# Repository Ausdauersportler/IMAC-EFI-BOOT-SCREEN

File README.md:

# IMAC-EFI-BOOT-SCREEN

How to create an EFI boot screen vBIOS for Apple 2009 to Mid 2011 iMac systems using AMD MXM3 graphics cards

My goal is to provide a comprehensive guide how to construct EFI BIOS versions for some AMD MXM cards. As described in detail in this [thread](https://forums.macrumors.com/threads/2011-imac-graphics-card-upgrade.1596614/post-17425857) owners of modular Apple iMac models built in 2009-2011 with MXM slot graphcs card can replace the original ATI card either with an Nvidia Kepler or an AMD GCN 1.0 to 4.0 card. While there has been a lot of success offering an EFI boot screen with NVIDIA cards development stuck with the AMD cards at some point where an iMac firmware modification has been proposed. Although the firmware modification is quite simple the adoption rate is frankly speaking zero. IMHO this is still the best way to go. Nevertheless even this method will need a BIOS constructed in the same way as described here within the wiki. 

Just to complete this introduction: 
Lately [improvements](https://forums.macrumors.com/threads/imac-2011-maxwell-and-pascal-gpu-upgrade.2300989/post-30017630) have been made to add a NVIDIA Maxwell and Pascal card, but please note there are no macOS drivers available within any macOS versions starting with Mojave, and there is limited EFI boot screen support.

The [wiki](https://github.com/Ausdauersportler/IMAC-EFI-BOOT-SCREEN/wiki) decribes tools, sources, methods, orignal limitations, solutions and state of the current development.  

## iMac models supported

This repository is limited to these eight iMac models published from 2009 to 2011:

- iMac9,1 Early 2009 A1225 24 inch (LVDS) (using a modified EnableGop9,1 driver, see note 1)
- iMac10,1 Late 2009 A1311 21.5 inch (LVDS) (see note 2)

- iMac10,1 Late 2009 A1312 27 inch (eDP, see note 3 about EG2)

- iMac11,1 Late 2009 A1312 27 inch (eDP)
- iMac11,2 Mid 2010 A1311 21.5 inch (eDP)
- iMac11,3 Mid 2010 A1312 27 inch (eDP)

- iMac12,1 Mid 2011 A1311 21.5 inch (eDP)
- iMac12,2 Mid 2011 A1312 27 inch (eDP)

Notes: 

1. Finally it was possible to include the iMac9,1 Mid 2009 A1225 24 inch to this list. The [2.93 GHz](https://everymac.com/systems/apple/imac/specs/imac-core-2-duo-3.06-24-inch-aluminum-early-2009-specs.html) and [3.06 GHz](https://everymac.com/systems/apple/imac/specs/imac-core-2-duo-2.93-24-inch-aluminum-early-2009-specs.html) versions were equipped with MXM3 slots and non metal graphics cards (GT120, GT130, AMD 4850). Best cards to use are the AMD FirePro M4000, M5100, W5170M, and M6000. The power hungry Saturn cards M6100 and W6170M/W6150M will over heat the system under load rapidly. This system needs a special EnableGop91 driver. All vBIOS files are marked aka named like this and include the LVDS string, too. Some more recent NVIDIA MXM3 cards may still have LVDS signaling support and therfore may work with these iMac9,1 system, too (never tested).

2. vBIOS file names contain the string LVDS, but not show the EnableGop91 string (see note 1). Unfortunately all more recent AMD GPUS starting the the Polaris/GCN4 architecture lack LVDS signaling hardware support. Therefore you cannot get those cards to display the boot screen unless you connect the internal display using a third party display driver board the external DP port - making it an externally connected display.

3. EG2 versions of vBIOS do not run on iMac10,1 A1312 systems, you get only a white screen in power on/boot. EG versions support all types of Macs listed.

4. Althout one cannot modify the legacy part of the vBIOS it is possible to inject a modified legacy vBIOS (the first 64K of it) using an SSDT or OpenCore DeviceProperties (ATY,bin_image) to enable the backlight control on Big Sur and Monterey. This mod does not apply or work with any Windows installation. Adding the EnableGop driver brought back EFI boot screen support. First and only replacement card which enables both external display connectors on iMac12,2.

5. Same method as described above enables virtual brightness control on RX6600M. Although values in ioreg and NVRAM are changed the brightness of the display itself does not change, probably because MXM PINS 23,25,27 are not connected as described in this [video](https://www.bilibili.com/video/BV1Ec411d7z6). Additionally the GOP driver has to be patched with the [Syncretic tool](https://forums.macrumors.com/threads/amd-radeon-rx-6800-xt-6900-xt-for-macos.2262295/page-36?post=31039294#post-31039294). Unfortunately neither EnableGop not OpenCore are able to switch on the internal backlight, so the display comes to life late at the login screen. 

## AMD graphcis cards supported

Currently we have tested these cards and can confirm the method works with:

- AMD FirePro M4000
- AMD FirePro M5100
- AMD FirePro M6000
- AMD FirePro W5170M

- AMD FirePro M6100
- AMD FirePro W6150M
- AMD FirePro W6170M

- AMD FirePro W7170M 
- AMD FirePro S7100X

- AMD Radeon Pro WX4130 mobile
- AMD Radeon Pro WX4150 mobile
- AMD Radeon Pro WX4170 mobile

- AMD Radeon Pro WX3200 mobile

- AMD Radeon Pro RX470 mobile
- AMD Radeon Pro RX480 mobile
- AMD Radeon Pro WX7100 mobile

- AMD Radeon Pro RX5500XT mobile (see note 4 above)
- AMD Radeon Pro RX6600M mobile (see note 5 above)

## Hardware upgrade (wiki)

You will find an [overwiew](https://github.com/Ausdauersportler/IMAC-EFI-BOOT-SCREEN/wiki/WWWW) which card works in which iMac and how to start the upgrade project and some more hardware related information about minor soldering tasks needed for a few cards to make them fully compatible in a newly added hardware section.

## Credits

Most knowledge has been gathered by me from contributions made by [Nick [D]vB](https://github.com/iMacGFX), [nikey22](https://github.com/nikey22), and [internetzel](https://github.com/internetzel) who spent some nights to explain everything in detail to me and who has much more patience to dive deeply into this matter than I do. Hope he will join me to fill this repository with contents. Last but not least thanks to [dfranetic](https://github.com/franetic), he finished what I could not have done. Great team!

Thanks to [rthpjm](https://forums.macrumors.com/members/rthpjm.535915/) for finding a W6150M and the necessary legacy vBIOS in some HP firmware update. Special thanks to [edwardgeo](https://forums.macrumors.com/members/edwardgeo.1274066/) for countless ideas and incredible knowledge about indepth AMD vBIOS modifications. All the best if these dark times!

[m0bil](https://github.com/m0bil) has become the expert for all NVIDIA modifications and probably he should start a similar repository about it and more importantly to this project he is the undisputed master of all iMac firmware modifications.

Finally many thanks to [Mike Beaton](https://github.com/mikebeaton) who developed an EFI driver named [EnableGop](https://github.com/mikebeaton/OpenCorePkg/tree/master/Staging/EnableGop) usable for both MacPro5,1 and modular iMacs as listed above using either Nvidia or AMD graphics cards to enable the EFI boot picker. I had to modify this driver a little bit to make it work on the older (LVDS) iMac9,1 model. This change has not been included into the EnableGop source tree and you need to get the driver named EnableGop91 compiled from this page. It works as desigend, with AMD and likely with NVIDIA cards as well.

## Support

If you want to support the AMD (i)Mac vBIOS development or just buy me a coffee [donations](https://www.paypal.com/paypalme/Ausdauersportler) are greatly appreciated.

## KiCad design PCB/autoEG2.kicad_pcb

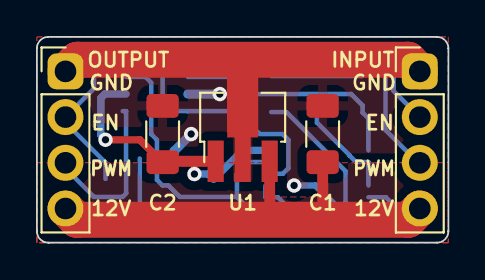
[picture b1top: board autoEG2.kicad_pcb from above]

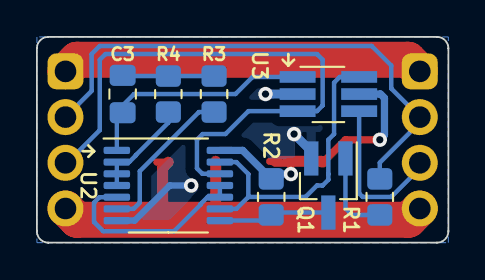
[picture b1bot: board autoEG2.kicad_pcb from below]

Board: 2 copper layers, 22.9 x 11.4 mm, 13 parts (8 on the bottom side), 14 nets.

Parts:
C1, C2: 1u; C_1206_3216Metric_Pad1.33x1.80mm_HandSolder
C3: 1nF; C_0805_2012Metric_Pad1.18x1.45mm_HandSolder
INPUT: Conn_01x04_Male; PinHeader_1x04_P2.54mm_Vertical
OUTPUT: Conn_01x04_Male; PinHeader_1x04_P2.54mm_Vertical
Q1: MMBT3904; SOT-23_Handsoldering
R1: 47k; R_0805_2012Metric_Pad1.20x1.40mm_HandSolder
R2: 22k; R_0805_2012Metric_Pad1.20x1.40mm_HandSolder
R3: 330k; R_0805_2012Metric_Pad1.20x1.40mm_HandSolder
R4: 33k; R_0805_2012Metric_Pad1.20x1.40mm_HandSolder
U1: L78L33; SOT-89-3_Handsoldering
U2: 74HC02; TSSOP-14_4.4x5mm_P0.65mm
U3: 74LVC1G157; TSOT-23-6_HandSoldering

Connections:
+12V: C1.1, INPUT.4, OUTPUT.4, U1.3 (IN)
/Q: U2.5, U2.10, U2.11
/R: Q1.3 (C), R2.2, U2.8
/S: INPUT.3, U2.12, U3.3 (I0)
/~Q: U2.9, U2.13, U3.6 (S)
GND: C1.2, C2.2, INPUT.1, OUTPUT.1, Q1.2 (E), U1.2 (GND), U2.7 (GND), U3.2 (GND)
unnamed: C3.1, U2.1, U3.1 (I1)
unnamed: C3.2, R3.2, R4.2
unnamed: Q1.1 (B), R1.2
unnamed: INPUT.2, OUTPUT.2, R1.1
unnamed: R3.1, U2.6
unnamed: R4.1, U2.2, U2.3, U2.4
unnamed: OUTPUT.3, U3.4 (Y)
VCC: C2.1, R2.1, U1.1 (OUT), U2.14 (VCC), U3.5 (VCC)

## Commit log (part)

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2022-04-12 Update README.md
    Added W7170M/S7100X and applied some minor corrections.
2022-04-12 Create empty
2022-04-12 Add files via upload
    wiki documentation image
2022-04-12 Hex Fiend
    Searching the frame buffer name and supported device-id
2022-04-13 Add files via upload
    unmodified EFI module extracted from MacBookPro 15" 2015 firmware
2022-04-13 Add files via upload
    Modified version of the VenusEG2.efi as described in the documentation ready to use within the EFI BIOS.
2022-04-13 Add files via upload
    EFirom compressed version of M370.efi with device-id 0x6820.
2022-04-13 Add files via upload
    EFIrom macOS executable (terminal, in case you cannot start it adjust permissions using chmod)
2022-04-13 Add files via upload
    modules ready to inject into iMac firmware
2022-04-13 Add files via upload
    CoreEG2 and EDIDParser modules in EFI format (just a different header compared to the similar ffs modules uploaded). These files can be used with OpenCore.
2022-04-13 Add files via upload
    W5170M iMac compatible GOP BIOS ((c) Ausdauersportler 2021)
2022-04-13 Add files via upload
    iMac compatible EG2 BIOS ((c) Ausdauersportler 2021)
2022-04-13 Add files via upload
    Replace the GOP with the Apple EG2 BIOS
2022-04-14 Add files via upload
    Amethyst and Saturn wire-mod to enable the internal backlight on boot. Using a switch to select this constant 3V feed and the modulated PWM signal during normal use (normal wiring) makes it an option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
2022-06-24 Update README.md
    Added M4000 after the first reader brought to an end what I started back last year, thanks a lot!
2022-08-19 Add files via upload
    EFI Boot screen capable vBIOS on iMacs with EG2 modded firmware.
2022-08-19 Add files via upload
    Apple legacy vBIOS dumped from ioregistry explorer
2022-08-24 Add files via upload
    Table of default values for some connector variables Mac M370 GPU
2022-08-25 Create UGA
2022-08-26 Delete Ghidra-EFI-Byte-Code-Processor - A Ghidra processor module for the EFI Byte Code (EBC).URL
    Added link to tools section
2022-10-19 Add files via upload
    Added the LVTMA table from the W7170M vBIOS to the legacy part to enable brightness control.
2022-10-26 Update README.md
    iMac10,1 does not show the EFI picker on the internal screen, instead POST hangs on a white screen, backlight is enabled, though
2022-10-26 Create empty.rom
    Repository for EFI modded vBIOS files
2022-10-26 Add files via upload
    VRAM support for M5100
2022-10-27 Add files via upload
    AMD GOP driver used in all GOP vBIOS versions to be used with OpenCore in UEFI/Drivers section
2022-10-27 Create add-onPCB
2022-10-27 add-on PCB KiCad design files
2022-10-27 Add files via upload
    RX470 vBIOS modified to enable the internal LCD (experimental, never tried)
2022-10-27 Add files via upload
    RX470 GOP, OBJ_INFO changed, never tested, 262KB chip size format
2022-10-27 Add files via upload
    new VRAM_INFO for WX7100
2022-10-27 Add files via upload
    RX480
2022-10-28 Add files via upload
    experimental, never tested
2022-10-30 Create empty.rom
    create folder to store original video BIOS versions used here
2022-11-01 add-on PCB schematic
2022-11-02 add-on PCB cable connections
2022-11-02 corrected color coding
2022-11-08 W6150M
    Both the W5160M and the modified 4GB version of the W6179M vBIOS run on the iMac and provide OpenCore boot screen support.
2022-11-08 W6150M
    W6170M-4GB-EG2_adj.rom will work on iMacs with EG2 firmware modification running a W6150M card
2022-11-08 W6150M (runs also with this W6170M-4GB version)
2022-11-18 Add files via upload
    User SEJU came up with another card supporting different VRAM. Mode details later.
2022-11-18 Add files via upload
    Original (SEJU) and ALT_VRAM (IDENIX)
2022-11-25 RX5500XT MXM
    This is already an GOP vBIOS. Since we cannot modify the legacy part and cannot fix the OBJ_INFO module to adapt one connector to eDP I will not upload a fixed GOP vBIOS. Please to not flash on diffe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
2022-11-25 RX5500XT
    RX5500XT Navi 14 compatible EG2 driver pulled from MP7,1 firmware
    Convert with `EfiRom -ec NV14Python_EG2.efi -l 0x30000 -f 0x1002 -i 0x7340 -p -o NV14Python_EG2_.rom` into EG2 rom and exchange with existing GOP. Needs iMac EG2 modded firmware to provide an EFI Boo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
2022-11-26 Update README.md
    added notes for 2009 iMac10,1
2022-11-29 UEFI Windows support
    You need BootCamp drivers installed and the driver signature patch applied to avoid error 43.
    Alternatively you can always try to install legacy Windows via DVD since the EFI picker is working now (not tested).
2022-11-29 UEFI Windows support
2022-11-29 W7170M
    Special thanks to @nikey22!
2022-11-29 Windows 10 UEFI / Legacy
    Tested this version after applying @nikey22 patch. Works fine with Windows 10 and perfectly with EFI boot picker on EG2 modded iMac.
2022-11-29 UEFI Windows 10
    added @nikey22 head patch to enable AMD drivers to recognize the card properly
2023-01-23 Add files via upload
    Hex Fiend TCL template to parse the AMD PCIR video BIOS header
2023-01-23 Add files via upload
    W5170M GOP vBIOS legacy header before starting the VGA cutting process
2023-01-23 Add files via upload
    Header of W5170M vBIOS after cutting out the VGA part and after adjusting image size, directory and table addresses properly.
2023-01-23 Add files via upload
    W5170M BIOS Header after deleting VGA part and fixing addresses
2023-01-23 Add files via upload
    W5170M BIOS header after cutting the VGA part and fixing addresses
2023-01-23 Add files via upload
    W5170M Data and Command Tables
2023-01-23 Create emtpy
2023-01-23 Add files via upload
    Full EFI vBIOS for W5170M card.
2023-02-24 Update README.md
    added information about LVDS based systems.
2023-02-27 EnableGop
2023-03-04 Folder for Apple vBIOS versions
2023-03-04 Apple 4670 and 4850 vBIOS
    eDP (iMac11,1 and iMac11,2)
    LVDS (iMac10,1 21.5 and iMac9,1 24)
2023-03-05 Add files via upload
    New OBJ_Info module no longer needing OpenCore connectors and connector-count entries.
2023-03-05 GCN upload
    W7170M untested, may brick your card!
2023-03-09 LVDS fixes
2023-03-12 WX4130 GCN4 (alt VRAM support)
2023-03-14 W6170M 2GB
2023-03-14 WX41X0 4GB
2023-03-16 Removed last image indicator
2023-03-16 removed last image indicator bit
2023-03-17 experimental and not tested
    - please be ready to clip flash in case of trouble
2023-03-18 not tested
2023-04-02 GCN performance upload
    EnableGop Version 1.2 and PIN_LUT correction to enable full performance
2023-04-02 LVDS upload
    W5170 with EnableGop 1.2 and LVDS support (iMac9,1 OC picker only, iMac10,1 EFI picker)
2023-04-03 Rename Readme.md to AReadme.md
2023-04-03 Rename AReadme.md to Readme.md
2023-04-04 W5170M SMBUS fix
    How to avoid SMBUS problems.
2023-04-04 EG 1.2
    M6100 Obj_Info and EnableGop 1.2
2023-04-04 EG 1.2
    EnableGop 1.2 and M6100 Obj_Info
2023-04-04 Add files via upload
    M6100 Obj_Info
2023-04-04 EG 1.2 - still untested
2023-04-06 RX5500XT
2023-04-06 LVDS upload
    potential iMac9,1 24 replacement for ATI 4850 and GT130 (both MXM3-B)
2023-04-06 EG 1.2
2023-04-06 LVDS EG 1.2
2023-04-20 WX7100 (not tested)
    This the the EG version of the WX7100-GOP.rom published in the GOP folder. If you currently use the GOP version chances are good with new vBIOS might enable the EFI Boot screen for you, too.
2023-04-24 LVDS EG 1.3
2023-05-11 iMac9,1 EFI boot screen version
    Please use until further notice only on iMac9,1 24" models with MXM3 slot!
2023-05-12 iMac9,1 EFI boot screen version
2023-05-13 iMac9,1 EFI support
    Note about adding iMac9,1 EFI boot screen support using a modified EnableGop driver.
2023-05-18 adding iMac9,1 EFI support
2023-08-21 ATOMTableResize re-upload
    The original on overclock.net is no longer available for download.
2023-09-08 WX7100 with alternate VRAM support (EG1.1)
2023-10-15 Added VRAM support
    This M6100 version contains another VRAM module apparently supporting all types of Hynix, Samsung, and Elpida memory. EFI boot screen support with EnableGop driver included.
2023-10-15 M6100 simplified VRAM support
    This M6100 version contains another VRAM module apparently supporting all types of Hynix, Samsung, and Elpida memory. EFI boot screen support with EnableGop driver included.
2023-10-15 Update EG driver support information
2023-11-24 2nd alternative VRAM support
    WX4150 and WX4170 version with Hynix AJR memory - in case neither the normal or ALT version work properly give this a try. As usual an EnableGop version offers EFI Boot picker support.
2024-06-09 Update README.md
    some Sunday morning corrections
2024-06-12 Update README.md
    fixed a dead link, added comments on EnableGop9,1
2024-10-16 hardware mods #1
    modifications needed for all blue HP WX4150 and WX3200 cards
2024-10-16 hardware mod #2
    WX4170: how to add a BIOS chip
2024-10-16 W5170M modification
    for iMac11,2 and iMac9,1 (LVDS)
2024-10-19 Update README.md
    added hardware section to wiki
2024-11-26 Update README.md
    added RX6600M comment
2025-03-08 AMD WX3200 EG
    This is the EnableGop version providing an EFI boot picker as all versions in this folder.
    It needs still the AMD Lexa spoofing enabled by OCLP, but *no* AMG GOP injection - it was never necessary when using files from this repository.
2025-03-12 AMD RX480 EG
    EnableGop driver, 67W for cooler run time behavior, Windows UEFI support
2025-08-20 Update Readme.md
    Minor clarification about EnableGop driver versions. All cards will work using the first public release 1.1.
2025-08-20 4GB VRAM version
    The first RX5500XT-EnableGop file supports 8GB VRAM, only. The new version (speaking names) supports 4GB VRAM. The EnableGop driver version 1.4 has been used. Both cards need the PCB @franetic develo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
2025-09-11 hardware mod #3
2025-10-07 hardware mod #4
